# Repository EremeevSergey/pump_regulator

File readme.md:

# Реле контроля уровня.
## Описание.

Позволяет контролировать уровень жидкости (откачивать/закачивать). Для контроля используются датчики с ***сухим контактом***, например:

+ [Датчик уровня жидкости герконовый](https://market.yandex.ru/product--poplavkovyi-vykliuchatel-priamoi/1811578569?sku=101921281993&do-waremd5=M3t-M77g-mPceoP2A7weeg&uniqueId=986967)
+ [Поплавковый герконовый датчик уровня воды](https://www.ozon.ru/product/liquid-level-switch-m15-poplavkovyy-gerkonovyy-datchik-urovnya-vody-zhidkosti-rezba-m15-kabel-688831200/)
+ [Поплавковый выключатель, контроль уровня воды]( https://market.yandex.ru/product--poplavkovyi-vykliuchatel-priamoi/1811578569?sku=101921281993&do-waremd5=M3t-M77g-mPceoP2A7weeg&uniqueId=986967)

Можно использовать нормально разомкнутые, нормально замкнутые контакты, а также и те и другие одновременно  (программируется каждый контакт индивидуально). Выход Реле имеет контакт нормально-замкнутый и нормально-разомкнутые контакты. 

Изначально Реле (устройство) разрабатывалось для откачки воды, но оно может быть использовано и для наполнения воды.

## Органы управления и индикации.

**Назначение клемм указано на рисунке.** Следует отметить, что клеммы 1, 3 внутри соединены между собой.

**L1, L2 - светодиоды, показывающие состояния датчиков (1 и 2 соответственно)**

| Цвет светодиода  | Описание                                           |
|------------------|----------------------------------------------------|
| Красный          | Датчик сработал                                    |
| Зеленый          | Датчик не сработал (контакт нормально-разомкнутый), т.е. контакт разомкнут.|
| Синий            | Датчик не сработал (контакт нормально-замкнутые), т.е. контакт замкнут |

**K1, K2 - кнопки управления**

Долгое нажатие (10 сек. и дольше) на одну из кнопок переключает тип датчика с нормально-разомкнутого на нормально-замкнутый и наоборот. Тип датчика сохраняется даже после отключения питания. Для нормально-разомкнутого контакта в несработанном состоянии светодиод горит Зеленым цветом, а для нормально-замкнутого - Синим.

Если нажать и удерживать (10 сек. и дольше) одновременно две кнопки, то Реле переключиться с автоматического на ручной режима работы (и наоборот).
При переходе в ручной режим работы выход Реле отключается. Режим работы не запоминается и при включении, всегда устанавливается автоматический режим.

В ручном режиме работы кнопка K1 включает выходное Реле, а кнопка K2 - выключает. Для возврата в автоматический режим надо либо отключить питание (секунды на 2-3) либо нажать и удерживать (10 сек. и дольше) одновременно две кнопки K1 и K2. 

**LM - светодиод состояния выходного реле**
| Цвет светодиода  | Описание                                     |
|------------------|----------------------------------------------|
| Красный горит    | Выходного реле включено                      |
| Зеленый горит    | Выходного реле (автоматический режим работы) |
| Синий   горит    | Выходного реле (ручной режим работы)         |

Если светодиод моргает (не важно каким цветом), значит Реле не смогло правильно прочитать из внутренней памяти (или записать в память) тип датчика. В этом случае тип всех контактов всегда будет нормально-разомкнутым. Вообще такое вряд-ли может случиться, т.к. ресурс флэш-памяти микроконтроллера реле позволят записывать не менее 100 000 раз. Чтобы затереть ячейки флэш-памяти надо будет очень часто менять типы контактов датчиков.

## Подключение.
### Откачиваем воду.
Схема подключения приведена ниже.

Самый правильный вариант, это поставить нормально-разомкнутые контакты (Датчик 1 и Датчик 2). В данном случае насос будет включаться только когда уровень воды поднимется выше Датчика 2 и будет откачивать воду пока её уровень не опустится ниже Датчика 1, или пропадёт напряжение питания (после восстановления питания, откачка воды возобновиться только, когда уровень воды опять поднимется выше датчика 2).

Если нет нормально-разомкнутых датчиков, можно поставить и нормально-замкнутые. В это случае надо будет кнопками К1, К2 поменять тип датчика (см. выше). 

### Набираем воду.

Как упоминалось в начале, Реле изначально разрабатывалось для откачки воды. Поэтому для обеспечения наборы воды есть несколько вариантов, каждый из которых имеет нюансы:

1. Назовём этот вариант "агрессивный". Т.е., если при включении  уровень воды будет ниже Датчика 2, насос включится и будет работать пока не "докачает" воду до Датчика 2. Далее он выключиться до тех пор пока уровень воды не спадёт до уровня Датчика 1. 

Подключение аналогично схеме "откачки воды", только насос подключаем к замкнутому выходному контакту Реле а не к разомкнутому.

Этот вариант меня смущает тем, что мы подключаем насос к нормально-замкнутым выходным контактам (см. схему). Вроде и ничего, но .... а вдруг Реле "сдохнет". Тогда с большей вероятностью выход отключиться, но т.к. насос подключен к нормаль-замкнутым контактам, он будет работать, пока мы его из сети не выключим.

2. Назовём это вариант "ленивый".
В данном варианте мы меняем местами датчики, и кнопками "инвертируем" состояния датчиков (программируем, см. выше), т.е. если у нас стоят нормально-разомкнутые контакты, мы их переводим в режим нормально-замкнутых, и наоборот. Насос подключаем через нормально-разомкнутые контакты Реле (как и при откачки воды).

При такой схеме включения насос будет включаться только, если уровень воды опуститься ниже Датчика 2, и работать до тех пор, пока уровень воды не достигнет Датчика 1. Здесь у нас нет минуса первого варианта, но то, что мы меняем тип контакта, возможно может сбить с толку. Мне данный вариант кажется более надежным и оптимальным.

[Кое-что про изготовление](docs/build.md)

[Для тех, кто будет переделывать (дорабатывать)](docs/info.md)

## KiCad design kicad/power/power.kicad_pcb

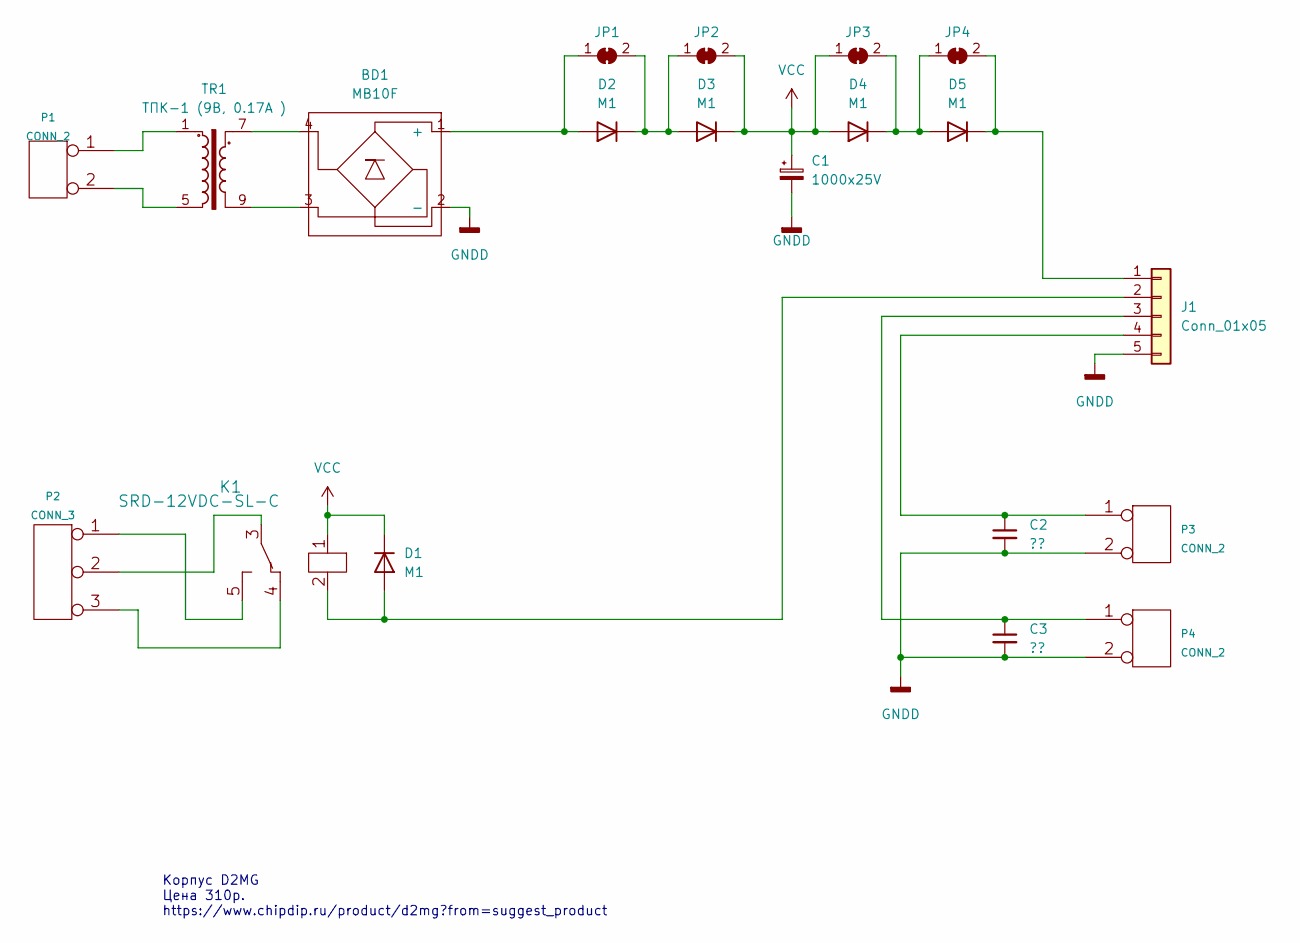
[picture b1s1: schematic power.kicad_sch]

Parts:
BD1: MB10F; MB-F
C1: 1000x25V; CP_Radial_D10.0mm_P5.00mm
C2, C3: ??; C_1206_3216Metric
D1, D2, D3, D4, D5: M1; D_SMA
J1: Conn_01x05; JST_EH_B5B-EH-A_1x05_P2.50mm_Vertical
JP1, JP2, JP3, JP4: SolderJumper_2_Bridged; SolderJumper-2_P1.3mm_Bridged_Pad1.0x1.5mm
K1: SRD-12VDC-SL-C
P1, P3, P4: CONN_2; KF128-2P
P2: CONN_3; KF128-3P
TR1: ТПК-1 (9В, 0.17А ); ТПК-1

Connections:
GNDD: BD1.2 (-), C1.2, C2.2, C3.2, J1.5, P3.2 (PM), P4.2 (PM)
unnamed: BD1.1 (+), D2.2 (A), JP1.1 (A)
unnamed: BD1.3, TR1.9
unnamed: BD1.4, TR1.7
unnamed: C2.1, J1.4, P3.1
unnamed: C3.1, J1.3, P4.1
unnamed: D1.2 (A), J1.2, K1.2 (in2)
unnamed: D2.1 (K), D3.2 (A), JP1.2 (B), JP2.1 (A)
unnamed: D4.1 (K), D5.2 (A), JP3.2 (B), JP4.1 (A)
unnamed: D5.1 (K), J1.1, JP4.2 (B)
unnamed: K1.3 (out2), P2.2
unnamed: K1.4 (out1), P2.3
unnamed: K1.5 (out3), P2.1
unnamed: P1.1, TR1.1
unnamed: P1.2 (PM), TR1.5
VCC: C1.1, D1.1 (K), D3.1 (K), D4.2 (A), JP2.2 (B), JP3.1 (A), K1.1 (in1)

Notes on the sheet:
Корпус D2MG Цена 310р. https://www.chipdip.ru/product/d2mg?from=suggest_product

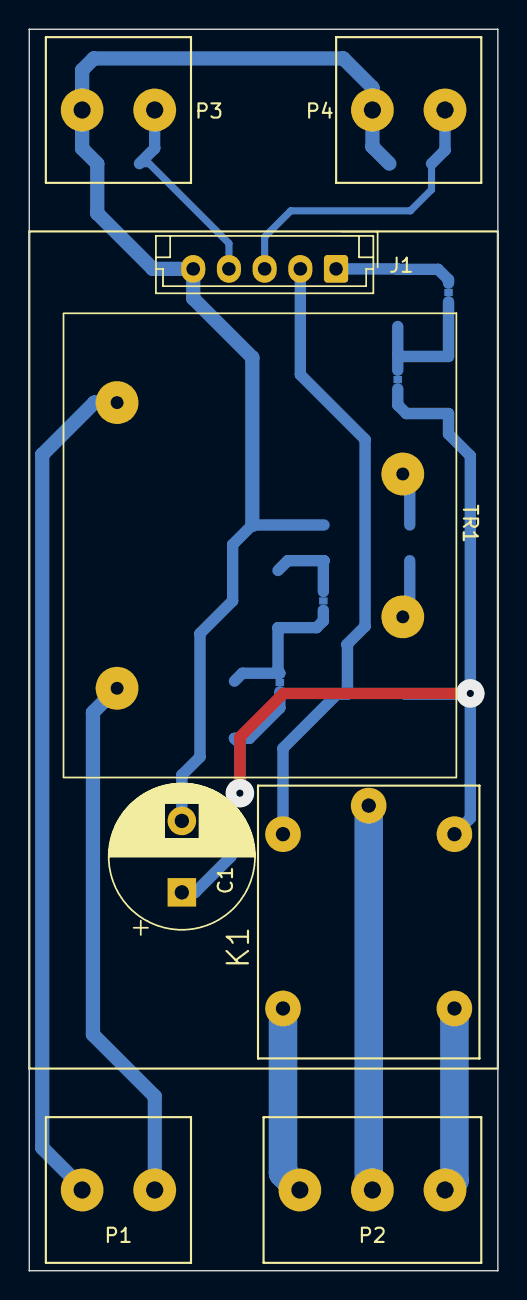
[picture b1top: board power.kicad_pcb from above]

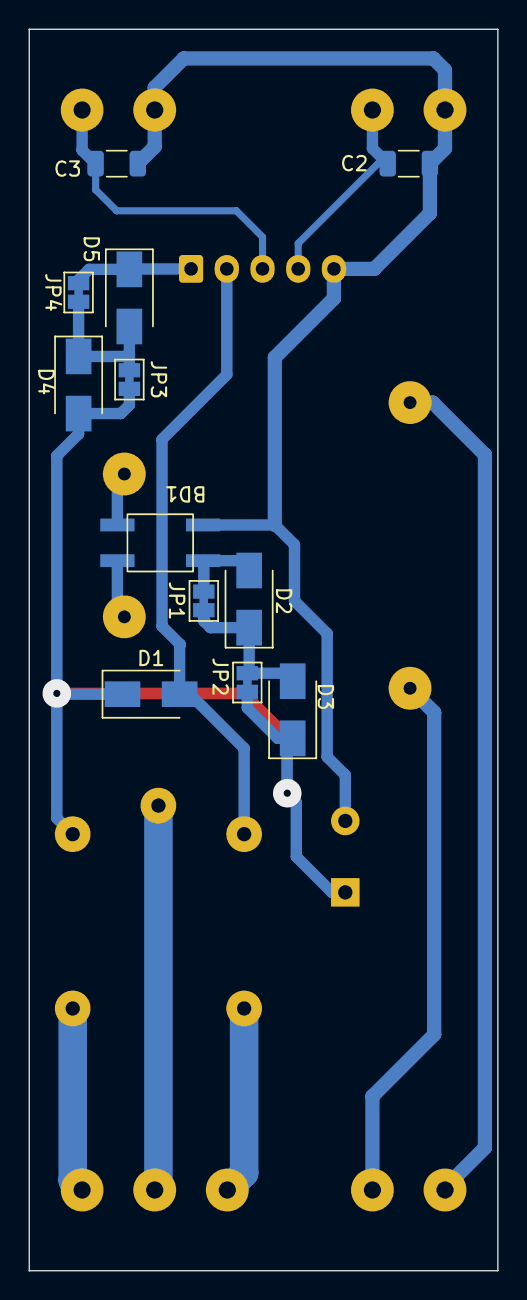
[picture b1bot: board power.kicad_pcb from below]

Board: 2 copper layers, 32.8 x 86.9 mm, 20 parts (12 on the bottom side), 16 nets.

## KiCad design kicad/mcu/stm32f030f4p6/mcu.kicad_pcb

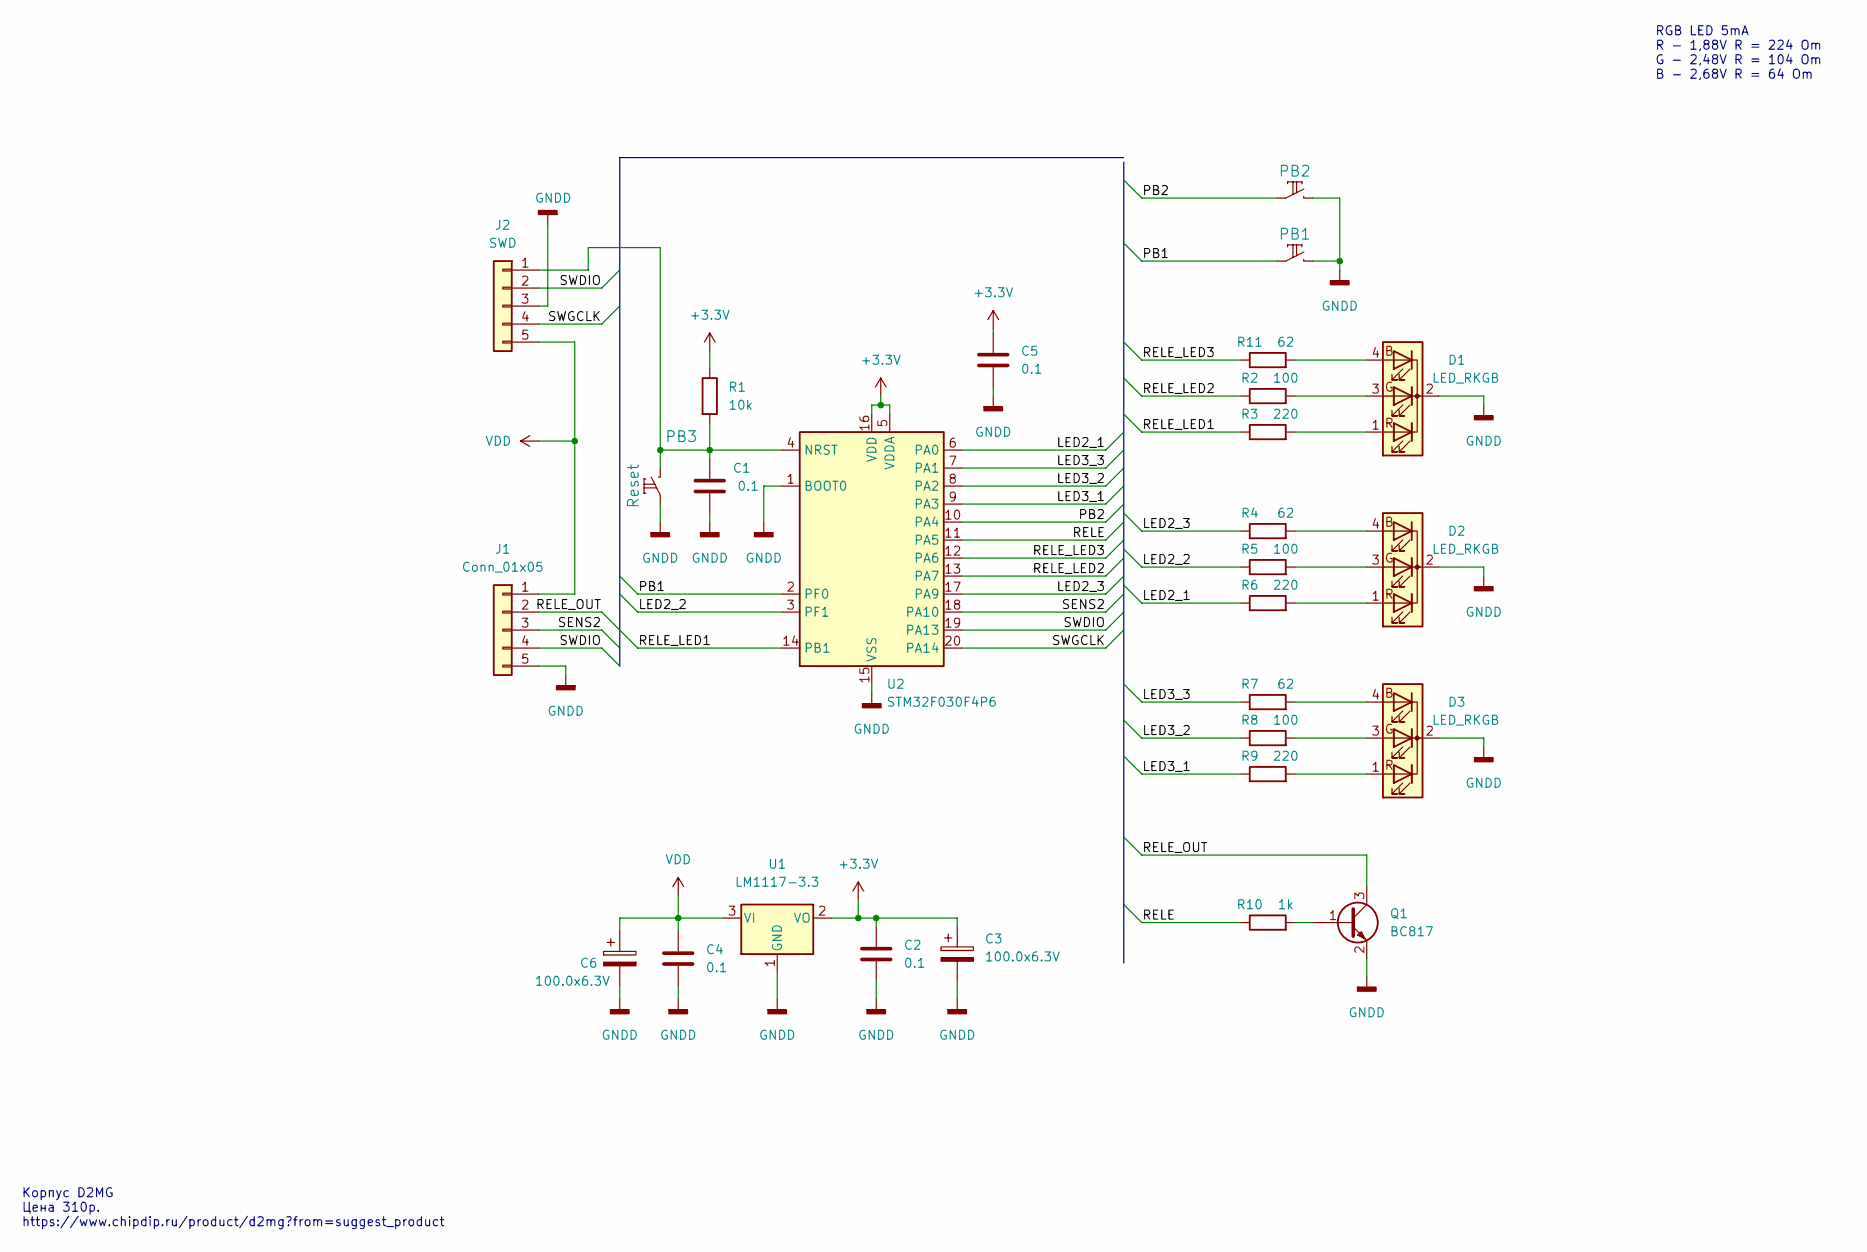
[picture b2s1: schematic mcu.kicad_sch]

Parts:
C1, C2, C4, C5: 0.1; C_1206_3216Metric
C3, C6: 100.0x6.3V; CP_EIA-3528-21_Kemet-B_Pad1.50x2.35mm_HandSolder
D1, D2, D3: LED_RKGB; LED_D5.0mm-4_RGB_Staggered_Pins
J1: Conn_01x05; JST_EH_B5B-EH-A_1x05_P2.50mm_Vertical
J2: SWD; JST_EH_B5B-EH-A_1x05_P2.50mm_Vertical
PB1, PB2: кнопка; SW_PUSH_6mm
PB3: Reset; PB_SMD_3x6x2.5
Q1: BC817; SOT-23
R1: 10k; R_1206_3216Metric
R2, R5, R8: 100; R_1206_3216Metric
R3, R6, R9: 220; R_1206_3216Metric
R4, R7, R11: 62; R_1206_3216Metric
R10: 1k; R_1206_3216Metric
U1: LM1117-3.3; SOT-223-3_TabPin2
U2: STM32F030F4P6; TSSOP-20_4.4x6.5mm_P0.65mm

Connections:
+3.3V: C2.1, C3.1, C5.1, R1.1, U1.2 (VO), U2.5 (VDDA), U2.16 (VDD)
/LED2_1: R6.1, U2.6 (PA0)
/LED2_2: R5.1, U2.3 (PF1)
/LED2_3: R4.1, U2.17 (PA9)
/LED3_1: R9.1, U2.9 (PA3)
/LED3_2: R8.1, U2.8 (PA2)
/LED3_3: R7.1, U2.7 (PA1)
/PB1: PB1.2, U2.2 (PF0)
/PB2: PB2.2, U2.10 (PA4)
/RELE: R10.1, U2.11 (PA5)
/RELE_LED1: R3.1, U2.14 (PB1)
/RELE_LED2: R2.1, U2.13 (PA7)
/RELE_LED3: R11.1, U2.12 (PA6)
/RELE_OUT: J1.2, Q1.3 (C)
/SENS2: J1.3, U2.18 (PA10)
/SWDIO: J1.4, J2.2, U2.19 (PA13)
/SWGCLK: J2.4, U2.20 (PA14)
GNDD: C1.1, C2.2, C3.2, C4.2, C5.2, C6.2, D1.2 (K), D2.2 (K), D3.2 (K), J1.5, J2.3, PB1.1, PB2.1, PB3.2, Q1.2 (E), U1.1 (GND), U2.1 (BOOT0), U2.15 (VSS)
unnamed: C1.2, J2.1, PB3.1, R1.2, U2.4 (NRST)
unnamed: D1.1 (RA), R3.2
unnamed: D1.3 (GA), R2.2
unnamed: D1.4 (BA), R11.2
unnamed: D2.1 (RA), R6.2
unnamed: D2.3 (GA), R5.2
unnamed: D2.4 (BA), R4.2
unnamed: D3.1 (RA), R9.2
unnamed: D3.3 (GA), R8.2
unnamed: D3.4 (BA), R7.2
unnamed: Q1.1 (B), R10.2
VDD: C4.1, C6.1, J1.1, J2.5, U1.3 (VI)

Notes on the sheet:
Корпус D2MG Цена 310р. https://www.chipdip.ru/product/d2mg?from=suggest_product
RGB LED 5mA R - 1,88V R = 224 Om G - 2,48V R = 104 Om B - 2,68V R = 64 Om

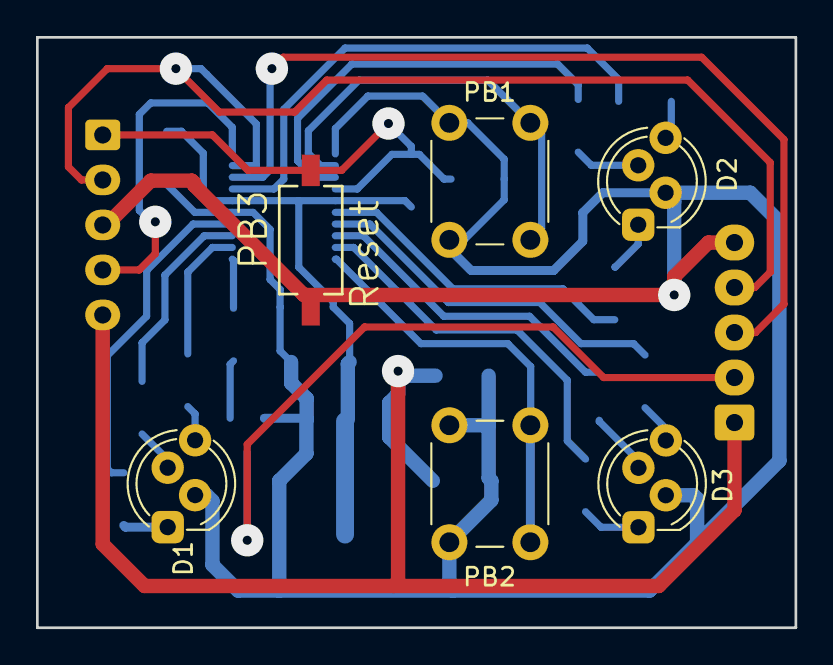
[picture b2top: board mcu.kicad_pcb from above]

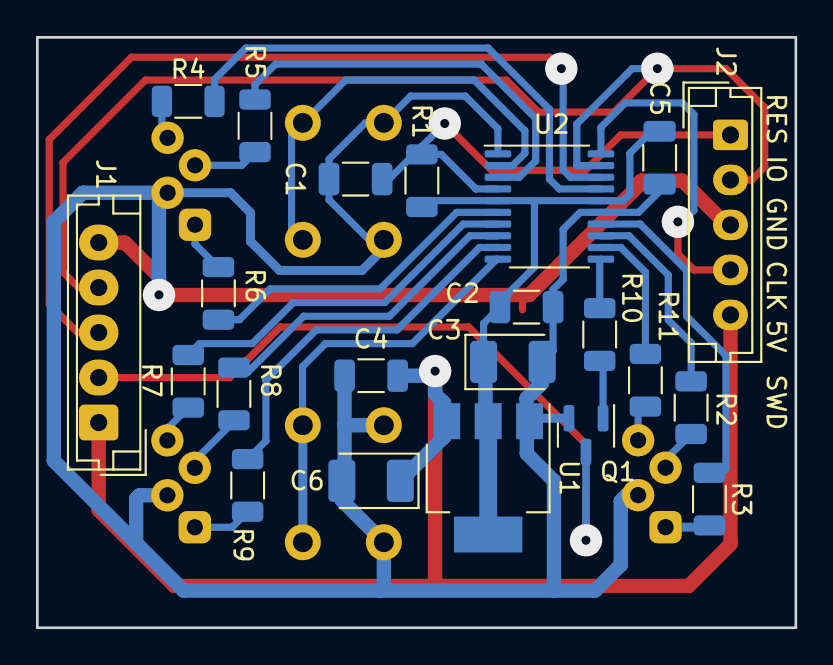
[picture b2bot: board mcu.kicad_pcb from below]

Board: 2 copper layers, 42.1 x 32.8 mm, 28 parts (22 on the bottom side), 30 nets.

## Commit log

2024-01-05 Поробуем на плате разместить eeprom
2024-01-22 пока без eeprom
2024-01-22 Немного каталоги перетусовал
2024-01-23 На питании диоды замкнул перемычками
2024-01-24 VER_0.0.0
2024-01-24 Забыл SWD 'выключить'
2024-01-24 Сенсоры перепутал-поправил. Усправил выход у Реле с OD на PP
2024-01-24 Добавил информаию по корпусу
2024-01-25 Косметика
2024-01-29 add docs
2024-01-30 Вроде конец
2024-01-30 V0.0.0
2024-01-31 Детали, стоимость
